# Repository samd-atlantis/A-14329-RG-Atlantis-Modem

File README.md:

# A-14329 RG Atlantis Modem

Hardware and development firmware for the Atlantis cellular gateway for Walchem controllers. The first ordered main board is **A-14329-MB00**.

The carrier combines an HLK-7628N Wi-Fi/router module, four Ethernet ports, a removable Quectel Mini PCIe cellular modem, USB-C service access and isolated AC power with parallel controller power terminals. Bluetooth and LoRa are omitted. MB00 uses the physical SIM; onboard eSIM U20 is an unpopulated future option.

## Current hardware snapshot

Start with `hardware/releases/A-14329-MB00/`. Its manifest identifies and hashes the latest saved EasyEDA schematic, PCB, assembly BOM/CPL and review evidence. The capture is the working design saved before this repository handoff; it is **not yet a verified copy of the exact files submitted with the PCB order**. Archive the actual order Gerbers, assembly selections and JLC order confirmation there when available.

`hardware/easyeda/` retains the full design history, routing scripts, references and intermediate exports for traceability. Proposed and intermediate files are not production inputs. `hardware/rev-a/kicad/` is an earlier concept and is not synchronized to MB00; do not fabricate it or treat its ERC as validation of the current board.

## Firmware

Start with [the programming procedure](firmware/PROGRAMMING-MB00.txt) and [firmware overview](firmware/README.txt). Source includes authenticated LuCI setup, QMI cellular networking, per-unit provisioning, four controller links and a visual preview. The separate GitHub cross-build produces credential-free development images; check its actual result and [validation record](firmware/VALIDATION-MB00.txt). No hardware boot test or production qualification is claimed. The target remains HLK-7628N, ramips/mt76x8, **32 MB flash**; confirm the fitted module's memory and partition layout before flashing.

[Factory provisioning](firmware/FACTORY-PROVISIONING.txt) prepares a private identity bundle for each unit using one common image. The fixture still needs first-board testing. Routine updates preserve identity and site configuration; factory reset of a common-image unit erases its writable identity and requires reprovisioning.

Run source checks:

```sh
python3 -m unittest discover -s firmware/tests -p 'test_*.py' -v
node firmware/tests/check.js
```

GitHub Actions runs these checks on Linux. They exercise mocked carrier control and UI behavior, not RF performance or physical hardware. The OpenWrt image build is a separate Linux build described in `firmware/README.txt`.

The build now pins OpenWrt **25.12.6**. After compilation, separate image checks inspect the actual kernel/device tree and installed filesystem against the exact build source. Check both workflow results; passing source tests alone does not establish a usable firmware image. The [factory recovery notes](firmware/HLK-FACTORY-RECOVERY.txt) distinguish USB serial console access from the arriving module's still-to-be-qualified initial loading procedure.

## Bring-up and release status

- Ordered modem is **EC25AFFA-MINIPCIE**. Its used interface pins match the carrier. J9 takes a **nano-SIM**; U20 remains absent. Actual carrier activation and modem firmware still need bench verification.
- Independent saved-design audit is complete: see [audit disposition](hardware/audits/AUDIT-MB00.txt). 285 critical pin checks passed; routed pad-bearing nets and native ground fills are connected. The current-geometry KiCad check found no short/clearance/drill errors under the translated rules, with documented warnings and translation limits.
- Q3's overlapping schematic wires have a separate corrected native candidate. The saved PCB assigns those pins correctly; frozen order-handoff files are unchanged. Import/review/ERC of the candidate remains necessary before a future schematic-to-PCB sync.
- Modem supply reserve remains a prototype hold: 116 µF nominal fitted versus Quectel's ≥470 µF Mini PCIe recommendation. The [power review](hardware/audits/mb00-electrical/power-addendum.txt) explains why blindly adding a capacitor is also inappropriate and gives the measurement/ECO plan.
- Validate physical-SIM default, USB host selection, regulator stability, LTE transmit supply droop, Ethernet center taps, all ports, Wi-Fi and recovery access.
- User confirmed 4 layers, 1.6 mm, 1 oz outer copper and JLC04161H-7628. Actual submitted Gerbers/BOM/CPL are still not reconciled. Verify 10 A temperature rise, terminal soldering/fit, isolation and enclosure fit before production release; the mains buses measure 4.064 mm with 1.7 mm terminal stems.
- ST1/ST2 JAE NT4R1600 supports are currently separate-source mechanical hardware, absent from JLC assembly BOM/CPL. Their conversion into actual assembly components is outstanding.
- [Atlantis portal](portal/README.md) now has a local customer preview, server-side site permissions, proxy configuration and staged WireGuard enrollment. Firmware source includes WireGuard; remote access remains disabled until a hub and unit keys are configured. No public WAN device ports are opened. Hosting, actual account/MFA enrollment and real-controller acceptance remain pending.

Keep per-unit passwords, SIM credentials, VPN keys, RF-calibration backups and provisioned images private. They are not repository deliverables. Third-party datasheets and libraries retain their original owners' rights; no blanket redistribution license is asserted.

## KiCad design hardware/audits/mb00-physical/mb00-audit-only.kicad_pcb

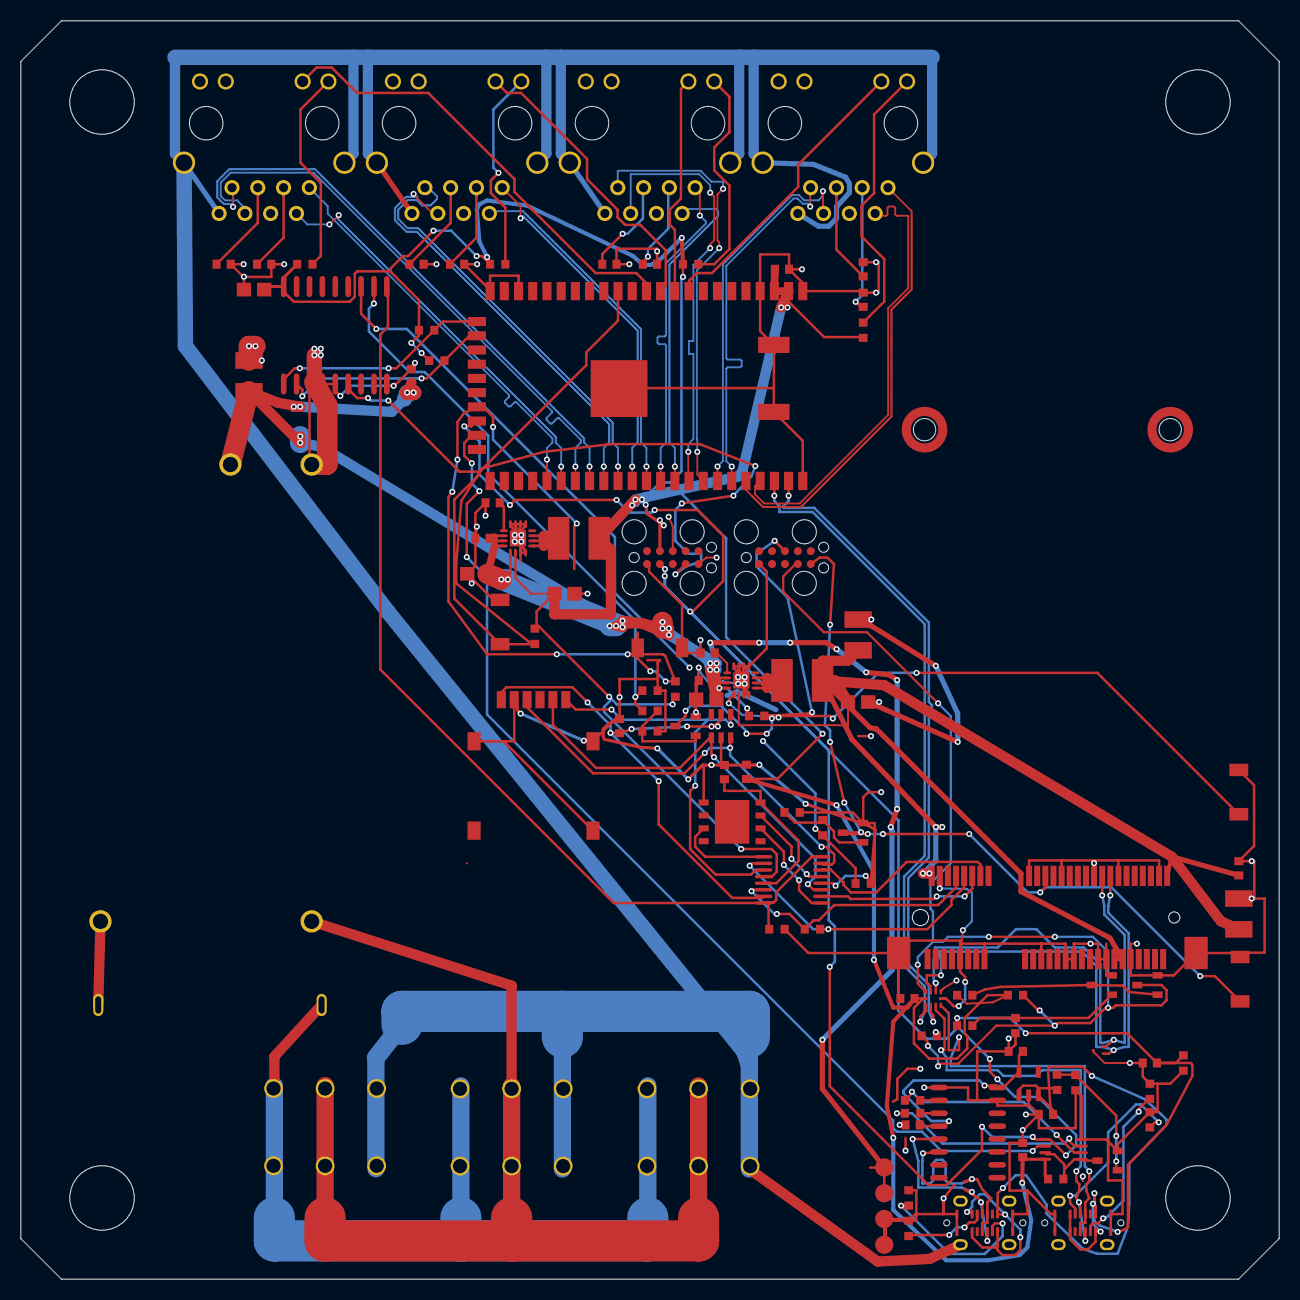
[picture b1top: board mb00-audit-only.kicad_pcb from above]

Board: 4 copper layers, 124.0 x 124.0 mm, 138 parts (0 on the bottom side), 93 nets.

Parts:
C1, C2, C10, C11, C12, C13, C20, C21, C22, C23, C24, C25, C30, C31, C41, C42, C43, C44, C51, C52, C53, C54, C60, C61, C70, C71, C72, C90, C91, C92, C93, C94: AUDIT_ONLY
CN1: AUDIT_ONLY
F1: AUDIT_ONLY
J2, J2.e25, J2.e26, J3, J3.e25, J3.e26, J4, J4.e25, J4.e26, J5, J5.e25, J5.e26, J8, J8.e126, J8.e127, J9, J14, J14.e55, J14.e56, J15, J16, J17, J17.e55, J17.e56: AUDIT_ONLY
L1, L2: AUDIT_ONLY
MODEM1: AUDIT_ONLY
PS1: AUDIT_ONLY
Q1, Q2, Q3, Q4, Q5: AUDIT_ONLY
R20, R21, R22, R30, R31, R32, R33, R35, R36, R37, R41, R42, R43, R44, R60, R61, R70, R74, R90, R91, R92, R93, R94, R95, R96, R97, R98, R99, R100, R101, R102, R103: AUDIT_ONLY
SW1, SW3, SW4, SW5: AUDIT_ONLY
TEST_PADS: AUDIT_ONLY
U1, U2, U3, U6, U8, U9, U10, U14, U15, U16, U17, U18, U19, U20: AUDIT_ONLY
ed270000000001f4, ed270000000001f6, ed270000000001f8, ed270000000001fa, ed26000000000931, ed26000000000936: AUDIT_ONLY
tc2050leg_00000b, tc2050leg_00000d, tc2050leg_00000f, tc2050leg_00001a, tc2050leg_00003c, tc2050leg_00003f, tc2050leg_000011, tc2050leg_000014, tc2050leg_000017, tc2050leg_000030, tc2050leg_000032, tc2050leg_000034, tc2050leg_000036, tc2050leg_000039: AUDIT_ONLY

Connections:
3V3_MODEM: C23.1, C24.1, C25.1, C61.1, J8.2, J8.39, J8.41, J8.52, L2.2, U3.14
3V3_ROUTER: C13.1, C30.1, C31.1, C60.1, C70.1, C93.1, L1.2, R30.1, R31.1, R36.1, R37.1, R41.1, R42.1, R43.1, R44.1, R92.1, R102.1, R103.1, TEST_PADS.H1-9, U1.2, U1.3, U2.14, U6.18, U8.10, U10.12, U18.8
5V_ISO: C1.1, C2.1, C10.1, C11.1, C20.1, C21.1, PS1.3, R20.1, TEST_PADS.3, TEST_PADS.4, U2.10, U2.11, U2.12, U2.13, U3.10, U3.11, U3.12
AC_L_FUSED: F1.2, PS1.2
AC_L_IN: CN1.1, F1.1, J15.1, J16.1
AC_N: CN1.2, J15.2, J16.2, PS1.1
CHASSIS_PE: CN1.3, J2.8, J2.13, J2.14, J3.8, J3.13, J3.14, J4.8, J4.13, J4.14, J5.8, J5.13, J5.14, J14.1, J14.2, J14.3, J14.4, J15.3, J16.3, J17.1, J17.2, J17.3, J17.4
CONSOLE_RX: TEST_PADS.H1-8, U1.32, U18.6
CONSOLE_TX: TEST_PADS.H1-2, U1.31, U18.5
GND_ISO: C1.2, C2.2, C10.2, C11.2, C12.2, C13.2, C20.2, C21.2, C22.2, C23.2, C24.2, C25.2, C30.2, C31.2, C41.2, C42.2, C43.2, C44.2, C51.2, C52.2, C53.2, C54.2, C60.2, C61.2, C70.2, C71.2, C72.2, C90.2, C91.2, C92.2, C93.2, C94.2, J8.4, J8.9, J8.15, J8.18, J8.21, J8.26, J8.27, J8.29, J8.34, J8.35, J8.37, J8.40, J8.43, J8.50, J8.MP1, J8.MP2, J9.5, J9.9, J9.10, J9.11, J14.A1, J14.A12, J14.B1, J14.B12, J17.A1, J17.A12, J17.B1, J17.B12, PS1.4, Q1.2, Q2.2, Q3.2, Q4.2, Q5.2, R22.2, R32.2, R33.2, R35.2, R61.2, R74.2, R90.2, R91.2, R93.2, R97.2, R98.2, R99.2, R101.2, SW1.2, SW3.2, SW4.2, SW5.2, TEST_PADS.1, TEST_PADS.2, TEST_PADS.H1-1, TEST_PADS.J12-1, U1.1, U1.4, U1.21, U1.23, U1.56, U1.57, U1.58, U1.59, U2.5, U2.6, U2.7, U2.8, U2.15, U2.16, U2.17, U3.5, U3.6, U3.7, U3.8, U3.15, U3.16, U3.17, U6.3, U6.4, U6.5, U6.9, U8.5, U9.3, U10.4, U14.2, U15.3, U16.1, U16.15, U17.2, U18.4, U19.3, U20.1
I2C_SCL: R30.2, U1.24, U6.1
I2C_SDA: R31.2, U1.25, U6.2
LAN1_GREEN_A: J2.9, R41.2
LAN1_LED_N: J2.10, U1.12
LAN1_RXN: J2.7, U1.41
LAN1_RXP: J2.6, U1.40
LAN1_RX_CT: C41.1, J2.5
LAN1_TXN: J2.2, U1.39
LAN1_TXP: J2.1, U1.38
LAN1_TX_CT: C51.1, J2.3
LAN2_GREEN_A: J3.9, R42.2
LAN2_LED_N: J3.10, U1.11
LAN2_RXN: J3.7, U1.43
LAN2_RXP: J3.6, U1.42
LAN2_RX_CT: C42.1, J3.5
LAN2_TXN: J3.2, U1.45
LAN2_TXP: J3.1, U1.44
LAN2_TX_CT: C52.1, J3.3
LAN3_GREEN_A: J4.9, R43.2
LAN3_LED_N: J4.10, U1.10
LAN3_RXN: J4.7, U1.49
LAN3_RXP: J4.6, U1.48
LAN3_RX_CT: C43.1, J4.5
LAN3_TXN: J4.2, U1.47
LAN3_TXP: J4.1, U1.46
LAN3_TX_CT: C53.1, J4.3
LAN4_GREEN_A: J5.9, R44.2
LAN4_LED_N: J5.10, U1.9
LAN4_RXN: J5.7, U1.51
LAN4_RXP: J5.6, U1.50
LAN4_RX_CT: C44.1, J5.5
LAN4_TXN: J5.2, U1.53
LAN4_TXP: J5.1, U1.52
LAN4_TX_CT: C54.1, J5.3
MODEM_BUCK_EN: Q1.3, R20.2, SW5.1, TEST_PADS.J12-8, U3.13
MODEM_OFF: R21.1, R33.1, U6.11, U8.6
MODEM_OFF_GATE: Q1.1, R21.2, R22.1
MODEM_PERST_N: J8.22, Q2.3, SW4.1, TEST_PADS.J12-5
MODEM_RESET_GATE: Q2.1, R60.2, R61.1
MODEM_RESET_REQ: R35.1, R60.1, U6.12
MODEM_USB_SEL: Q5.3, R74.1, R103.2, TEST_PADS.J12-4, U8.9
MUSB_CC1: J17.A5, R97.1
MUSB_CC2: J17.B5, R98.1
MUSB_DETECT_N: Q4.3, Q5.1, R102.2
MUSB_GATE: Q4.1, R100.2, R101.1
MUSB_VBUS: C94.1, J17.A4, J17.A9, J17.B4, J17.B9, R99.1, R100.1
M_SS: C22.1, U3.9
M_SW: L2.1, U3.1, U3.2, U3.3
ROUTER_GPIO0_N: R37.2, SW3.1, TEST_PADS.H1-5, U1.30
ROUTER_RESET_N: R36.2, SW1.1, TEST_PADS.H1-4, U1.14, U6.6
R_SS: C12.1, U2.9
R_SW: L1.1, U2.1, U2.2, U2.3
SIM_A_CLK: J9.3, U10.3, U14.1
SIM_A_IO: J9.7, U10.11, U14.4
SIM_A_RST: J9.2, U10.7, U14.3
SIM_A_VCC: C71.1, J9.1, U10.15, U14.5
SIM_B_CLK: U10.1, U20.6
SIM_B_IO: U10.9, U20.3
SIM_B_RST: U10.5, U20.7
SIM_B_VCC: C72.1, U10.13, U20.8
SIM_SELECT: R32.1, U6.10, U10.8, U10.16
USB_CONSOLE_DM: J14.A7, J14.B7, U16.6, U19.2
USB_CONSOLE_DP: J14.A6, J14.B6, U16.5, U19.1
USB_C_CC1: J14.A5, R90.1
USB_C_CC2: J14.B5, R91.1
USB_C_VBUS: C90.1, J14.A4, J14.A9, J14.B4, J14.B9, R94.1, U17.1, U17.3
USB_DETECT_GATE: Q3.1, R93.1, R94.2
USB_HOST_DM: U1.55, U8.2
USB_HOST_DP: U1.54, U8.1
USB_MODEM_DM: J8.36, U8.7, U9.2
USB_MODEM_DP: J8.38, U8.8, U9.1
USB_SERVICE_DM: J17.A7, J17.B7, U8.4, U15.2
USB_SERVICE_DP: J17.A6, J17.B6, U8.3, U15.1
USB_UART_3V3: C91.1, C92.1, U16.4, U16.16, U17.5
USB_UART_OE_N: Q3.3, R92.2, U18.1, U18.7
USB_UART_RX: R96.2, U16.3
USB_UART_RX_BUF: R96.1, U18.3
USB_UART_TX: R95.1, U16.2
USB_UART_TX_BUF: R95.2, U18.2
USIM_CLK: J8.12, U10.2
USIM_DATA: J8.10, R70.2, U10.10
USIM_RST: J8.14, U10.6
USIM_VDD: J8.8, R70.1, U10.14

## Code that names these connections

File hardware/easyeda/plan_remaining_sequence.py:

"""Sequential offline fragments, screened against previously accepted fragments."""
import json, subprocess, sys
from route_geometry import ROOT
jobs=[
 ('CONSOLE_RX','standalone','H1-3','U1','32',9.8425),
 ('ROUTER_RESET_N','standalone','H1-4','R36','2',9.8425),
 ('MODEM_PERST_N','standalone','J12-5','Q2','3',9.8425),
 ('MODEM_BUCK_EN','U3','13','R20','2',8),
 ('MODEM_BUCK_EN','standalone','J12-6','R20','2',9.8425),
 ('ROUTER_GPIO0_N','U1','30','R37','2',9.8425),
 ('ROUTER_GPIO0_N','standalone','H1-5','R37','2',9.8425),
 ('3V3_ROUTER','standalone','H1-6','R37','1',9.8425),
 ('3V3_ROUTER','R43','1','R42','1',16),
 ('3V3_ROUTER','C60','1','C70','1',16),
 ('3V3_ROUTER','C93','1','C60','1',16),
 ('USB_C_VBUS','J14','A9','C90','1',9.8425),
 ('MUSB_VBUS','J17','A9','C94','1',9.8425),
 ('MODEM_OFF','U8','6','R21','1',9.8425),
 ('SIM_A_VCC','U14','5','C71','1',9.8425),
 ('5V_ISO','C20','1','standalone','4',20),
]
priority=['MODEM_BUCK_EN','ROUTER_GPIO0_N','ROUTER_RESET_N','CONSOLE_RX','MODEM_PERST_N']
jobs=sorted(jobs,key=lambda j:priority.index(j[0]) if j[0] in priority else 20)
docs=json.loads((ROOT/'routing-native27-docs.json').read_text(encoding='utf-8'))
pcb=next(d['records'] for d in docs if d['head']['b']['docType']=='PCB')
source='routing-offline-sequence-docs.json';report=[];accepted=[]
for net,sref,spin,eref,epin,width in jobs:
 (ROOT/source).write_text(json.dumps(docs),encoding='utf-8')
 cmd=[sys.executable,str(ROOT/'plan_remaining_connection.py'),source,net,sref,spin,eref,epin,str(width),'1']
 result=subprocess.run(cmd,capture_output=True,text=True)
 filename=f'remaining-{net}-{sref}-{eref}-draft.json'
 status=dict(net=net,start=[sref,spin],end=[eref,epin],result=result.stdout.strip(),error=result.stderr.strip(),accepted=False)
 if result.returncode==0:
  draft=json.loads((ROOT/filename).read_text(encoding='utf-8'))
  if not draft['issues']:
   pcb.extend(draft['records']);accepted.extend(draft['records']);status['accepted']=True
 report.append(status)
 (ROOT/'remaining-sequence-report.json').write_text(json.dumps(report,indent=2))
 (ROOT/'remaining-sequence-fragment.json').write_text(json.dumps(dict(status='OFFLINE_NOT_APPLIED',records=accepted),indent=2))
 print(net,sref,eref,'ACCEPTED' if status['accepted'] else 'REVIEW',flush=True)
(ROOT/source).write_text(json.dumps(docs),encoding='utf-8')
